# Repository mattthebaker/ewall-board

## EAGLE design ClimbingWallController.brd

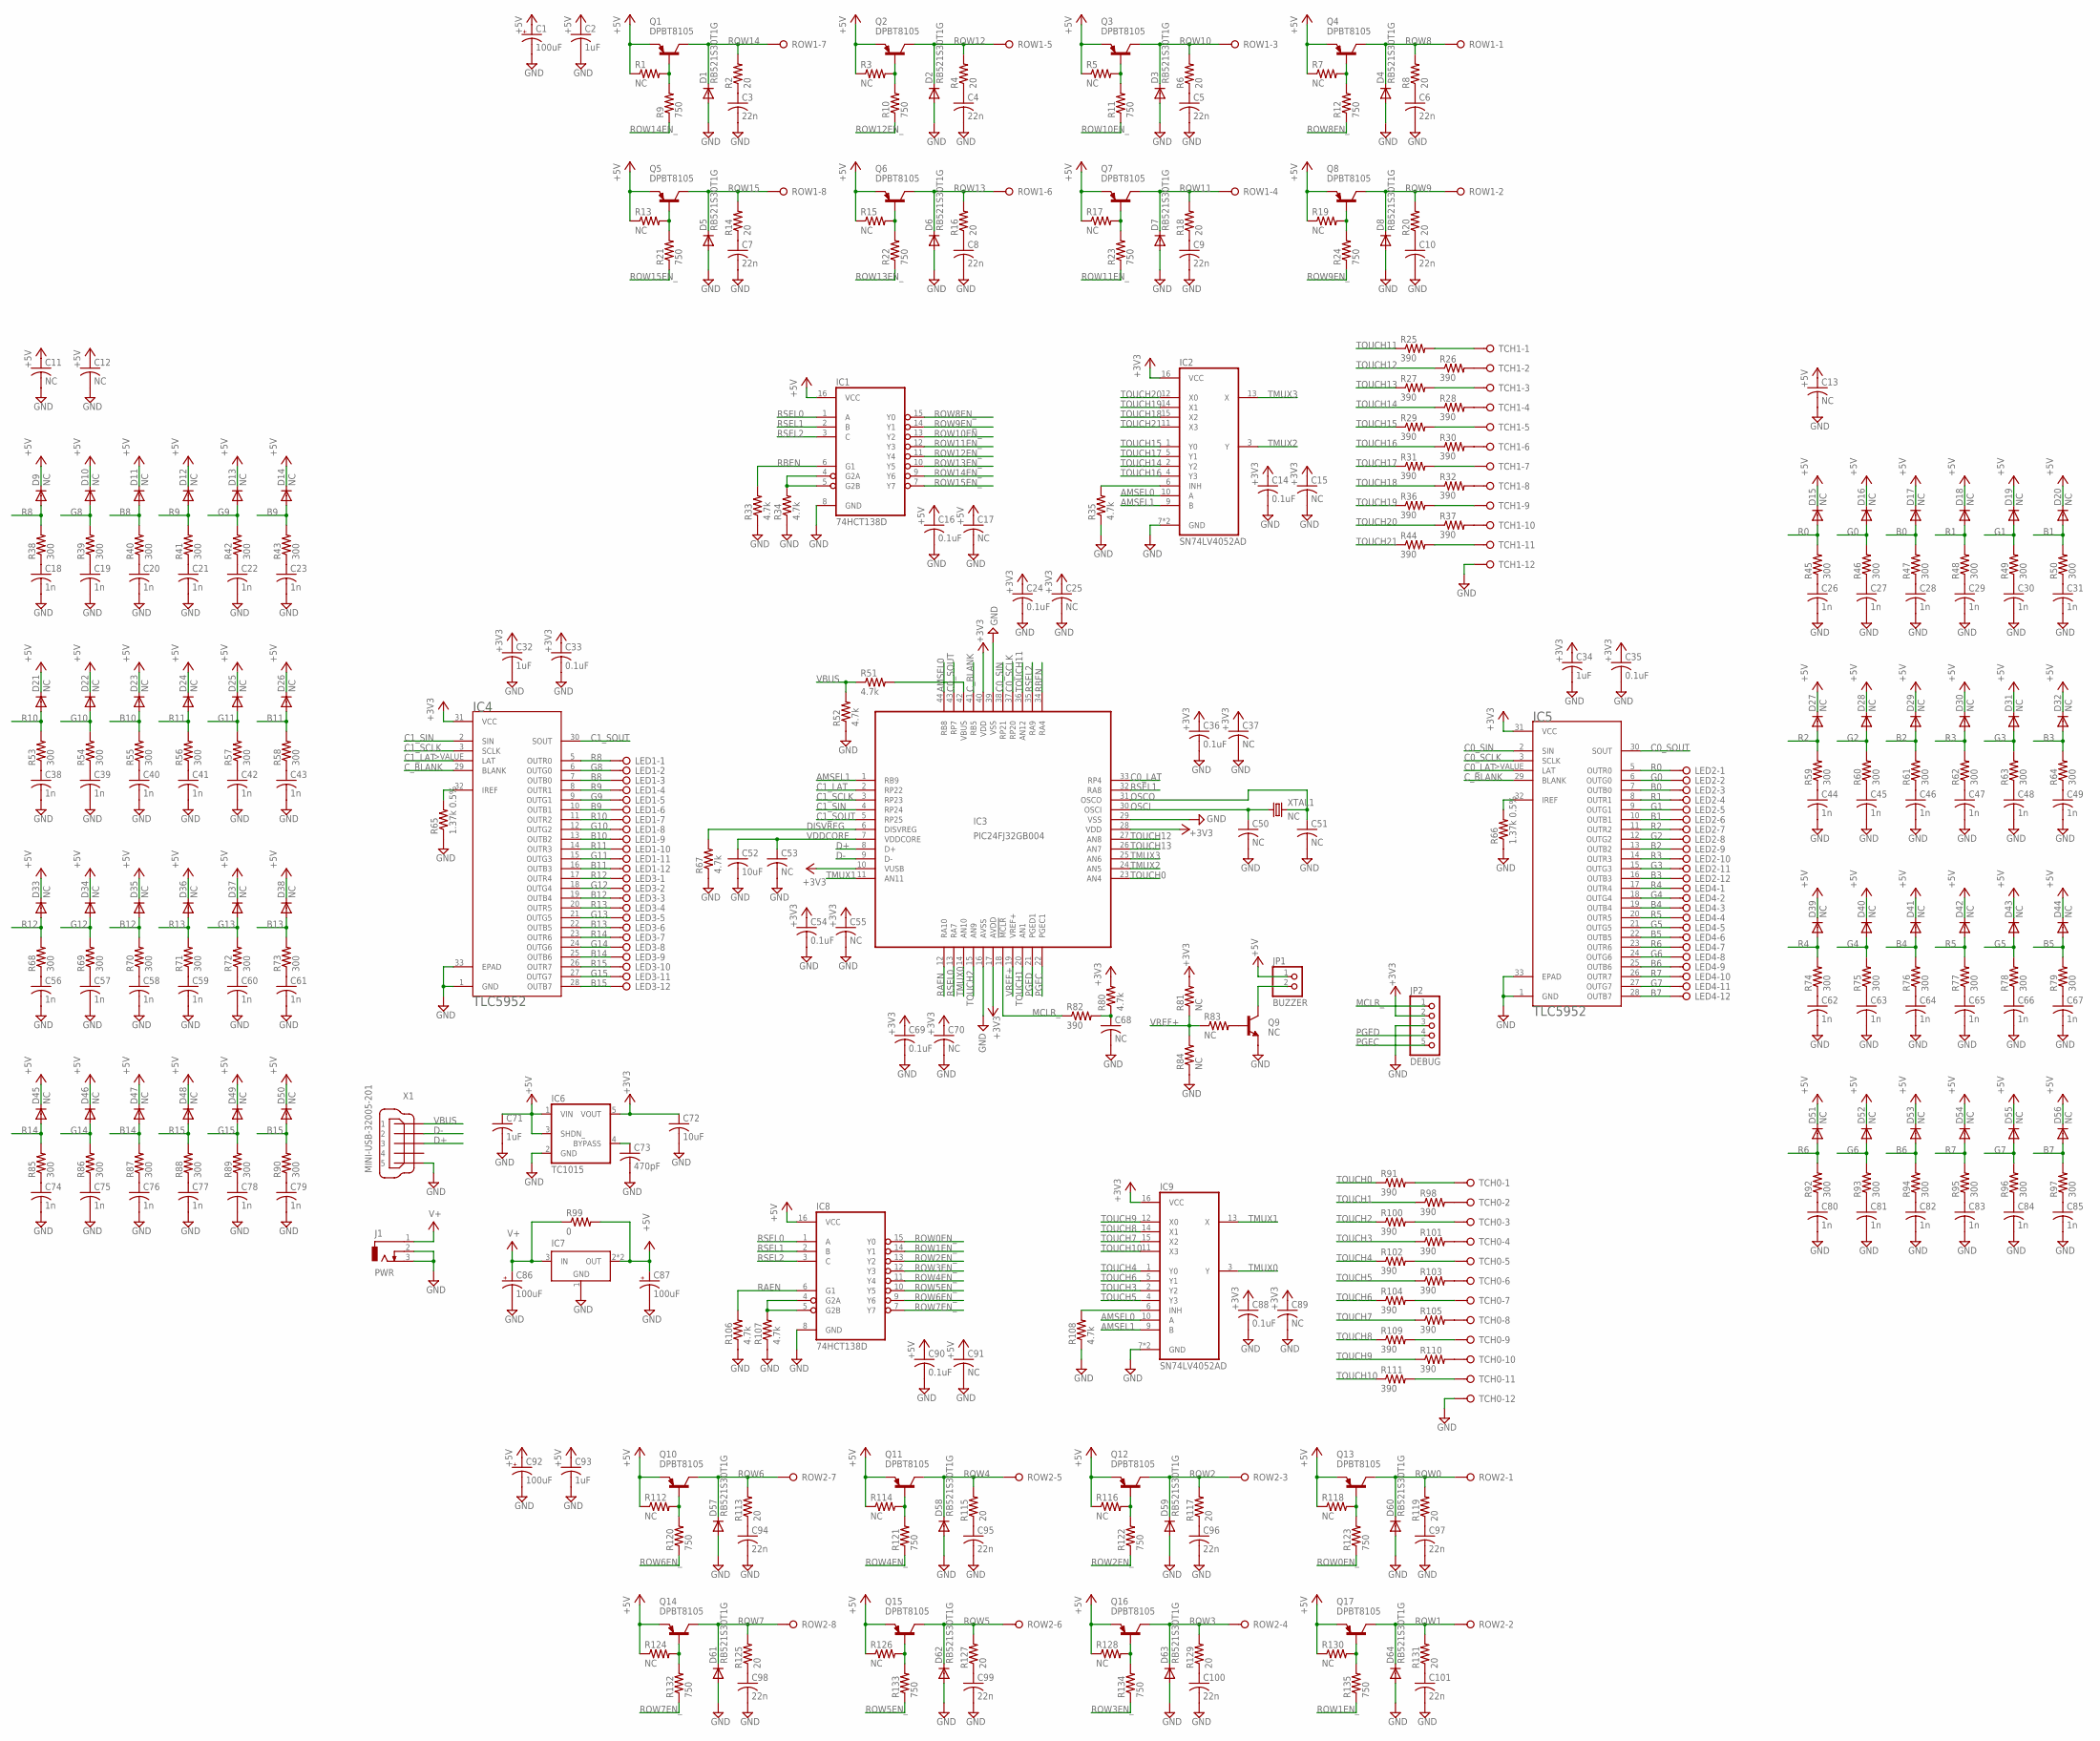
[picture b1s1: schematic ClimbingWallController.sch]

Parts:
C1, C86, C87, C92: 100uF; PANASONIC_D
C2, C32, C34, C71, C93: 1uF; C0603K
C3, C4, C5, C6, C7, C8, C9, C10, C94, C95, C96, C97, C98, C99, C100, C101: 22n; C0603K
C11, C12, C13, C15, C17, C25, C37, C50, C51, C53, C55, C68, C70, C89, C91: NC; C0603K
C14, C16, C24, C33, C35, C36, C54, C69, C88, C90: 0.1uF; C0603K
C18, C19, C20, C21, C22, C23, C26, C27, C28, C29, C30, C31, C38, C39, C40, C41, C42, C43, C44, C45, C46, C47, C48, C49, C56, C57, C58, C59, C60, C61, C62, C63, C64, C65, C66, C67, C74, C75, C76, C77, C78, C79, C80, C81, C82, C83, C84, C85: 1n; C0603K
C52, C72: 10uF; C1206K
C73: 470pF; C0603K
D1, D2, D3, D4, D5, D6, D7, D8, D57, D58, D59, D60, D61, D62, D63, D64: RB521S30T1G; SOD523
D9, D10, D11, D12, D13, D14, D15, D16, D17, D18, D19, D20, D21, D22, D23, D24, D25, D26, D27, D28, D29, D30, D31, D32, D33, D34, D35, D36, D37, D38, D39, D40, D41, D42, D43, D44, D45, D46, D47, D48, D49, D50, D51, D52, D53, D54, D55, D56: NC; SOD523
IC1, IC8: 74HCT138D; SO16
IC2, IC9: SN74LV4052AD; SO16
IC3: PIC24FJ32GB004; TQFP44
IC4, IC5: TLC5952; HTSSOP-32POWERPAD
IC6: TC1015; SOT23-5L
IC7: NCP1117; SOT223
J1: PWR; DCJ0303
JP1: BUZZER; 1X02
JP2: DEBUG; 1X05
LED1, LED2, LED3, LED4: OSTVN12A150; OSTVN12
Q1, Q2, Q3, Q4, Q5, Q6, Q7, Q8, Q10, Q11, Q12, Q13, Q14, Q15, Q16, Q17: DPBT8105; SOT23
Q9: NC; SOT23-BEC
R1, R3, R5, R7, R13, R15, R17, R19, R81, R83, R84, R112, R114, R116, R118, R124, R126, R128, R130: NC; R0603
R2, R4, R6, R8, R14, R16, R18, R20, R113, R115, R117, R119, R125, R127, R129, R131: 20; R0603
R9, R10, R11, R12, R21, R22, R23, R24, R120, R121, R122, R123, R132, R133, R134, R135: 750; R0603
R25, R26, R27, R28, R29, R30, R31, R32, R36, R37, R44, R82, R91, R98, R100, R101, R102, R103, R104, R105, R109, R110, R111: 390; R0603
R33, R34, R35, R51, R52, R67, R80, R106, R107, R108: 4.7k; R0603
R38, R39, R40, R41, R42, R43, R45, R46, R47, R48, R49, R50, R53, R54, R55, R56, R57, R58, R59, R60, R61, R62, R63, R64, R68, R69, R70, R71, R72, R73, R74, R75, R76, R77, R78, R79, R85, R86, R87, R88, R89, R90, R92, R93, R94, R95, R96, R97: 300; R0603
R65, R66: 1.37k 0.5%; R0805; TOLERANCE 0.5%
R99: 0; R0805
ROW1, ROW2: OSTVN08A150; OSTVN08
TCH0, TCH1: OSTVN12A150; OSTVN12
X1: MINI-USB-32005-201; 32005-201; MPN USB-M26FTR
XTAL1: NC; NX5032; MPN 7A-12.000MAAJ-T

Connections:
+3V3: C14.1, C15.1, C24.1, C25.1, C32.1, C33.1, C34.1, C35.1, C36.1, C37.1, C54.1, C55.1, C69.1, C70.1, C72.1, C88.1, C89.1, IC2.16 (VCC), IC3.10 (VUSB), IC3.17 (AVDD), IC3.28 (VDD), IC3.40 (VDD), IC4.31 (VCC), IC5.31 (VCC), IC6.5 (VOUT), IC9.16 (VCC), JP2.2, R80.2, R81.2
+5V: C1.+, C2.1, C11.1, C12.1, C13.1, C16.1, C17.1, C71.1, C87.+, C90.1, C91.1, C92.+, C93.1, D9.C, D10.C, D11.C, D12.C, D13.C, D14.C, D15.C, D16.C, D17.C, D18.C, D19.C, D20.C, D21.C, D22.C, D23.C, D24.C, D25.C, D26.C, D27.C, D28.C, D29.C, D30.C, D31.C, D32.C, D33.C, D34.C, D35.C, D36.C, D37.C, D38.C, D39.C, D40.C, D41.C, D42.C, D43.C, D44.C, D45.C, D46.C, D47.C, D48.C, D49.C, D50.C, D51.C, D52.C, D53.C, D54.C, D55.C, D56.C, IC1.16 (VCC), IC6.1 (VIN), IC6.3 (SHDN_), IC7.2 (OUT), IC7.4 (OUT), IC8.16 (VCC), JP1.1, Q1.2 (E), Q2.2 (E), Q3.2 (E), Q4.2 (E), Q5.2 (E), Q6.2 (E), Q7.2 (E), Q8.2 (E), Q10.2 (E), Q11.2 (E), Q12.2 (E), Q13.2 (E), Q14.2 (E), Q15.2 (E), Q16.2 (E), Q17.2 (E), R1.1, R3.1, R5.1, R7.1, R13.1, R15.1, R17.1, R19.1, R99.2, R112.1, R114.1, R116.1, R118.1, R124.1, R126.1, R128.1, R130.1
AMSEL0: IC2.10 (A), IC3.44 (RB8), IC9.10 (A)
AMSEL1: IC2.9 (B), IC3.1 (RB9), IC9.9 (B)
B0: D17.A, IC5.7 (OUTB0), LED2.3, R47.2
B1: D20.A, IC5.10 (OUTB1), LED2.6, R50.2
B2: D29.A, IC5.13 (OUTB2), LED2.9, R61.2
B3: D32.A, IC5.16 (OUTB3), LED2.12, R64.2
B4: D41.A, IC5.19 (OUTB4), LED4.3, R76.2
B5: D44.A, IC5.22 (OUTB5), LED4.6, R79.2
B6: D53.A, IC5.25 (OUTB6), LED4.9, R94.2
B7: D56.A, IC5.28 (OUTB7), LED4.12, R97.2
B8: D11.A, IC4.7 (OUTB0), LED1.3, R40.2
B9: D14.A, IC4.10 (OUTB1), LED1.6, R43.2
B10: D23.A, IC4.13 (OUTB2), LED1.9, R55.2
B11: D26.A, IC4.16 (OUTB3), LED1.12, R58.2
B12: D35.A, IC4.19 (OUTB4), LED3.3, R70.2
B13: D38.A, IC4.22 (OUTB5), LED3.6, R73.2
B14: D47.A, IC4.25 (OUTB6), LED3.9, R87.2
B15: D50.A, IC4.28 (OUTB7), LED3.12, R90.2
C0_LAT: IC3.33 (RP4), IC5.>VALUE (LAT)
C0_SCLK: IC3.37 (RP20), IC5.3 (SCLK)
C0_SIN: IC3.38 (RP21), IC5.2 (SIN)
C0_SOUT: IC3.43 (RP7), IC5.30 (SOUT)
C1_LAT: IC3.2 (RP22), IC4.>VALUE (LAT)
C1_SCLK: IC3.3 (RP23), IC4.3 (SCLK)
C1_SIN: IC3.4 (RP24), IC4.2 (SIN)
C1_SOUT: IC3.5 (RP25), IC4.30 (SOUT)
CAIREF: IC5.32 (IREF), R66.2
CAIREF1: IC4.32 (IREF), R65.2
C_BLANK: IC3.41 (RB5), IC4.29 (BLANK), IC5.29 (BLANK)
D+: IC3.8 (D+), X1.3
D-: IC3.9 (D-), X1.2
DISVREG: IC3.6 (DISVREG), R67.2
G0: D16.A, IC5.6 (OUTG0), LED2.2, R46.2
G1: D19.A, IC5.9 (OUTG1), LED2.5, R49.2
G2: D28.A, IC5.12 (OUTG2), LED2.8, R60.2
G3: D31.A, IC5.15 (OUTG3), LED2.11, R63.2
G4: D40.A, IC5.18 (OUTG4), LED4.2, R75.2
G5: D43.A, IC5.21 (OUTG5), LED4.5, R78.2
G6: D52.A, IC5.24 (OUTG6), LED4.8, R93.2
G7: D55.A, IC5.27 (OUTG7), LED4.11, R96.2
G8: D10.A, IC4.6 (OUTG0), LED1.2, R39.2
G9: D13.A, IC4.9 (OUTG1), LED1.5, R42.2
G10: D22.A, IC4.12 (OUTG2), LED1.8, R54.2
G11: D25.A, IC4.15 (OUTG3), LED1.11, R57.2
G12: D34.A, IC4.18 (OUTG4), LED3.2, R69.2
G13: D37.A, IC4.21 (OUTG5), LED3.5, R72.2
G14: D46.A, IC4.24 (OUTG6), LED3.8, R86.2
G15: D49.A, IC4.27 (OUTG7), LED3.11, R89.2
GND: C1.-, C2.2, C3.2, C4.2, C5.2, C6.2, C7.2, C8.2, C9.2, C10.2, C11.2, C12.2, C13.2, C14.2, C15.2, C16.2, C17.2, C18.2, C19.2, C20.2, C21.2, C22.2, C23.2, C24.2, C25.2, C26.2, C27.2, C28.2, C29.2, C30.2, C31.2, C32.2, C33.2, C34.2, C35.2, C36.2, C37.2, C38.2, C39.2, C40.2, C41.2, C42.2, C43.2, C44.2, C45.2, C46.2, C47.2, C48.2, C49.2, C50.2, C51.2, C52.2, C53.2, C54.2, C55.2, C56.2, C57.2, C58.2, C59.2, C60.2, C61.2, C62.2, C63.2, C64.2, C65.2, C66.2, C67.2, C68.2, C69.2, C70.2, C71.2, C72.2, C73.2, C74.2, C75.2, C76.2, C77.2, C78.2, C79.2, C80.2, C81.2, C82.2, C83.2, C84.2, C85.2, C86.-, C87.-, C88.2, C89.2, C90.2, C91.2, C92.-, C93.2, C94.2, C95.2, C96.2, C97.2, C98.2, C99.2, C100.2, C101.2, D1.A, D2.A, D3.A, D4.A, D5.A, D6.A, D7.A, D8.A, D57.A, D58.A, D59.A, D60.A, D61.A, D62.A, D63.A, D64.A, IC1.8 (GND), IC2.7 (GND), IC2.8 (GND), IC3.16 (AVSS), IC3.29 (VSS), IC3.39 (VSS), IC4.1 (GND), IC4.33 (EPAD), IC5.1 (GND), IC5.33 (EPAD), IC6.2 (GND), IC7.1 (GND), IC8.8 (GND), IC9.7 (GND), IC9.8 (GND), J1.2, J1.3, JP2.3, Q9.E, R33.1, R34.1, R35.1, R52.1, R65.1, R66.1, R67.1, R84.1, R106.1, R107.1, R108.1, TCH0.12, TCH1.12, X1.5
MCLR_: IC3.18 (!MCLR), JP2.1, R82.1
unnamed: Q13.1 (B), R118.2, R123.2
unnamed: C97.1, R119.1
unnamed: Q12.1 (B), R116.2, R122.2
unnamed: C96.1, R117.1
unnamed: Q16.1 (B), R128.2, R134.2
unnamed: C100.1, R129.1
unnamed: Q15.1 (B), R126.2, R133.2
unnamed: C99.1, R127.1
unnamed: Q11.1 (B), R114.2, R121.2
unnamed: C95.1, R115.1
unnamed: Q10.1 (B), R112.2, R120.2
unnamed: C94.1, R113.1
unnamed: Q14.1 (B), R124.2, R132.2
unnamed: C98.1, R125.1
unnamed: Q8.1 (B), R19.2, R24.2
unnamed: C10.1, R20.1
unnamed: Q4.1 (B), R7.2, R12.2
unnamed: C6.1, R8.1
unnamed: Q3.1 (B), R5.2, R11.2
unnamed: C5.1, R6.1
unnamed: Q7.1 (B), R17.2, R23.2
unnamed: C9.1, R18.1
unnamed: Q6.1 (B), R15.2, R22.2
unnamed: C8.1, R16.1
unnamed: Q2.1 (B), R3.2, R10.2
unnamed: C4.1, R4.1
unnamed: Q1.1 (B), R1.2, R9.2
unnamed: C3.1, R2.1
unnamed: Q5.1 (B), R13.2, R21.2
unnamed: C7.1, R14.1
unnamed: R98.2, TCH0.2
unnamed: R101.2, TCH0.4
unnamed: Q17.1 (B), R130.2, R135.2
unnamed: C101.1, R131.1
unnamed: R103.2, TCH0.6
unnamed: R105.2, TCH0.8
unnamed: R110.2, TCH0.10
unnamed: R26.2, TCH1.2
unnamed: R28.2, TCH1.4
unnamed: R30.2, TCH1.6
unnamed: IC8.4 (G2A), IC8.5 (G2B), R107.2
unnamed: IC9.6 (INH), R108.2
unnamed: IC1.4 (G2A), IC1.5 (G2B), R34.2
unnamed: IC2.6 (INH), R35.2
unnamed: IC3.42 (VBUS), R51.2
unnamed: C68.1, R80.1, R82.2
unnamed: R91.2, TCH0.1
unnamed: R32.2, TCH1.8
unnamed: R37.2, TCH1.10
unnamed: Q9.B, R83.2
unnamed: R100.2, TCH0.3
unnamed: R102.2, TCH0.5
unnamed: R104.2, TCH0.7
unnamed: R109.2, TCH0.9
unnamed: R111.2, TCH0.11
unnamed: R25.2, TCH1.1
unnamed: R27.2, TCH1.3
unnamed: R29.2, TCH1.5
unnamed: R31.2, TCH1.7
unnamed: R36.2, TCH1.9
unnamed: R44.2, TCH1.11
unnamed: C73.1, IC6.4 (BYPASS)
unnamed: JP1.2, Q9.C
unnamed: C26.1, R45.1
unnamed: C27.1, R46.1
unnamed: C28.1, R47.1
unnamed: C29.1, R48.1
unnamed: C30.1, R49.1
unnamed: C31.1, R50.1
unnamed: C44.1, R59.1
unnamed: C45.1, R60.1
unnamed: C46.1, R61.1
unnamed: C47.1, R62.1
unnamed: C48.1, R63.1
unnamed: C49.1, R64.1
unnamed: C62.1, R74.1
unnamed: C63.1, R75.1
unnamed: C64.1, R76.1
unnamed: C65.1, R77.1
unnamed: C66.1, R78.1
unnamed: C67.1, R79.1
unnamed: C80.1, R92.1
unnamed: C81.1, R93.1
unnamed: C82.1, R94.1
unnamed: C83.1, R95.1
unnamed: C84.1, R96.1
unnamed: C85.1, R97.1
unnamed: C18.1, R38.1
unnamed: C19.1, R39.1
unnamed: C20.1, R40.1
unnamed: C21.1, R41.1
unnamed: C22.1, R42.1
unnamed: C23.1, R43.1
unnamed: C38.1, R53.1
unnamed: C39.1, R54.1
unnamed: C40.1, R55.1
unnamed: C41.1, R56.1
unnamed: C42.1, R57.1
unnamed: C43.1, R58.1
unnamed: C56.1, R68.1
unnamed: C57.1, R69.1
unnamed: C58.1, R70.1
unnamed: C59.1, R71.1
unnamed: C60.1, R72.1
unnamed: C61.1, R73.1
unnamed: C74.1, R85.1
unnamed: C75.1, R86.1
unnamed: C76.1, R87.1
unnamed: C77.1, R88.1
unnamed: C78.1, R89.1
unnamed: C79.1, R90.1
OSCI: C50.1, IC3.30 (OSCI), XTAL1.P$1 (1)
OSCO: C51.1, IC3.31 (OSCO), XTAL1.P$2 (2)
PGEC: IC3.22 (PGEC1), JP2.5
PGED: IC3.21 (PGED1), JP2.4
R0: D15.A, IC5.5 (OUTR0), LED2.1, R45.2
R1: D18.A, IC5.8 (OUTR1), LED2.4, R48.2
R2: D27.A, IC5.11 (OUTR2), LED2.7, R59.2
R3: D30.A, IC5.14 (OUTR3), LED2.10, R62.2
R4: D39.A, IC5.17 (OUTR4), LED4.1, R74.2
R5: D42.A, IC5.20 (OUTR5), LED4.4, R77.2
R6: D51.A, IC5.23 (OUTR6), LED4.7, R92.2
R7: D54.A, IC5.26 (OUTR7), LED4.10, R95.2
R8: D9.A, IC4.5 (OUTR0), LED1.1, R38.2
R9: D12.A, IC4.8 (OUTR1), LED1.4, R41.2
R10: D21.A, IC4.11 (OUTR2), LED1.7, R53.2
R11: D24.A, IC4.14 (OUTR3), LED1.10, R56.2
R12: D33.A, IC4.17 (OUTR4), LED3.1, R68.2
R13: D36.A, IC4.20 (OUTR5), LED3.4, R71.2
R14: D45.A, IC4.23 (OUTR6), LED3.7, R85.2
R15: D48.A, IC4.26 (OUTR7), LED3.10, R88.2
RAEN: IC3.12 (RA10), IC8.6 (G1), R106.2
RBEN: IC1.6 (G1), IC3.34 (RA4), R33.2
ROW0: D60.C, Q13.3 (C), R119.2, ROW2.1
ROW0EN_: IC8.15 (Y0), R123.1
ROW1: D64.C, Q17.3 (C), R131.2, ROW2.2
ROW1EN_: IC8.14 (Y1), R135.1
ROW2: D59.C, Q12.3 (C), R117.2, ROW2.3
ROW2EN_: IC8.13 (Y2), R122.1
ROW3: D63.C, Q16.3 (C), R129.2, ROW2.4
ROW3EN_: IC8.12 (Y3), R134.1
ROW4: D58.C, Q11.3 (C), R115.2, ROW2.5
ROW4EN_: IC8.11 (Y4), R121.1
ROW5: D62.C, Q15.3 (C), R127.2, ROW2.6
ROW5EN_: IC8.10 (Y5), R133.1
ROW6: D57.C, Q10.3 (C), R113.2, ROW2.7
ROW6EN_: IC8.9 (Y6), R120.1
ROW7: D61.C, Q14.3 (C), R125.2, ROW2.8
ROW7EN_: IC8.7 (Y7), R132.1
ROW8: D4.C, Q4.3 (C), R8.2, ROW1.1
ROW8EN_: IC1.15 (Y0), R12.1
ROW9: D8.C, Q8.3 (C), R20.2, ROW1.2
ROW9EN_: IC1.14 (Y1), R24.1
ROW10: D3.C, Q3.3 (C), R6.2, ROW1.3
ROW10EN_: IC1.13 (Y2), R11.1
ROW11: D7.C, Q7.3 (C), R18.2, ROW1.4
ROW11EN_: IC1.12 (Y3), R23.1
ROW12: D2.C, Q2.3 (C), R4.2, ROW1.5
ROW12EN_: IC1.11 (Y4), R10.1
ROW13: D6.C, Q6.3 (C), R16.2, ROW1.6
ROW13EN_: IC1.10 (Y5), R22.1
ROW14: D1.C, Q1.3 (C), R2.2, ROW1.7
ROW14EN_: IC1.9 (Y6), R9.1
ROW15: D5.C, Q5.3 (C), R14.2, ROW1.8
ROW15EN_: IC1.7 (Y7), R21.1
RSEL0: IC1.1 (A), IC3.13 (RA7), IC8.1 (A)
RSEL1: IC1.2 (B), IC3.32 (RA8), IC8.2 (B)
RSEL2: IC1.3 (C), IC3.35 (RA9), IC8.3 (C)
TMUX0: IC3.14 (AN10), IC9.3 (Y)
TMUX1: IC3.11 (AN11), IC9.13 (X)
TMUX2: IC2.3 (Y), IC3.24 (AN5)
TMUX3: IC2.13 (X), IC3.25 (AN6)
TOUCH0: IC3.23 (AN4), R91.1
TOUCH1: IC3.20 (AN1), R98.1
TOUCH2: IC3.15 (AN9), R100.1
TOUCH3: IC9.2 (Y2), R101.1
TOUCH4: IC9.1 (Y0), R102.1
TOUCH5: IC9.4 (Y3), R103.1
TOUCH6: IC9.5 (Y1), R104.1
TOUCH7: IC9.15 (X2), R105.1
TOUCH8: IC9.14 (X1), R109.1
TOUCH9: IC9.12 (X0), R110.1
TOUCH10: IC9.11 (X3), R111.1
TOUCH11: IC3.36 (AN12), R25.1
TOUCH12: IC3.27 (AN8), R26.1
TOUCH13: IC3.26 (AN7), R27.1
TOUCH14: IC2.2 (Y2), R28.1
TOUCH15: IC2.1 (Y0), R29.1
TOUCH16: IC2.4 (Y3), R30.1
TOUCH17: IC2.5 (Y1), R31.1
TOUCH18: IC2.15 (X2), R32.1
TOUCH19: IC2.14 (X1), R36.1
TOUCH20: IC2.12 (X0), R37.1
TOUCH21: IC2.11 (X3), R44.1
V+: C86.+, IC7.3 (IN), J1.1, R99.1
VBUS: R51.1, R52.2, X1.1
VDDCORE: C52.1, C53.1, IC3.7 (VDDCORE)
VREF+: IC3.19 (VREF+), R81.1, R83.1, R84.2

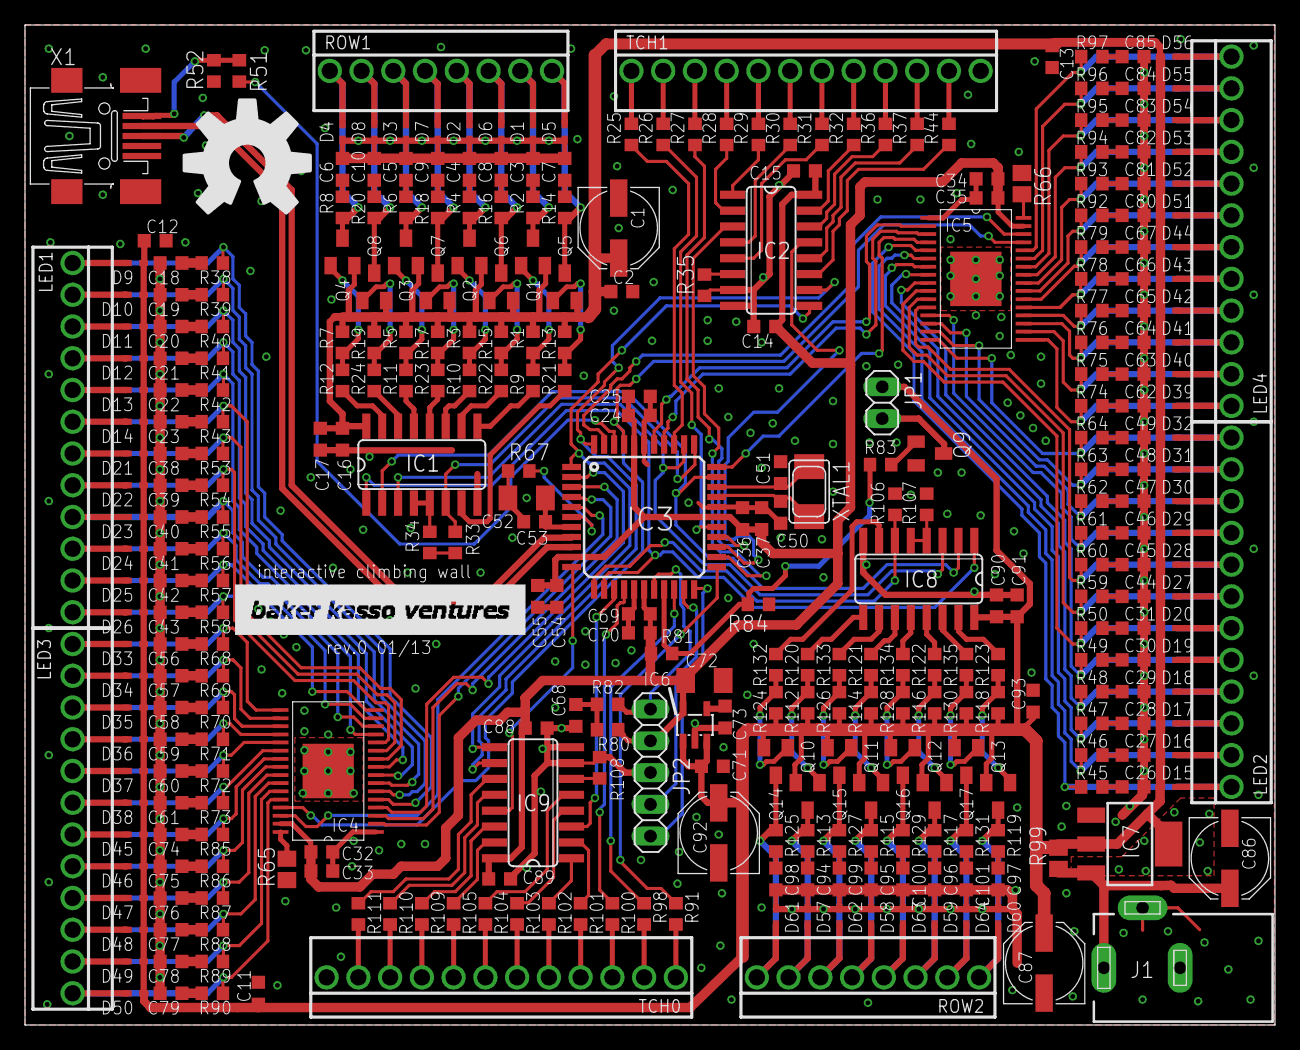
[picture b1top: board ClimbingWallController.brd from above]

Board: 2 copper layers, 100.0 x 80.0 mm, 339 parts (0 on the bottom side), 250 nets.
